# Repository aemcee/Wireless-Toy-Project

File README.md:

# Wireless-Toy-Project
ATmega328P based custom remote and unit (receiver) boards on arduino framework that will communicate over RF and with the following feature set: SD Card, RTC, Ultrasonic sensor, motor control, audio amplification w/audio jack or 8ohm speaker, motor control, LEDs

Remote PCB will replace current board in toy remote housing and receiver board will have custom 3D printed housing

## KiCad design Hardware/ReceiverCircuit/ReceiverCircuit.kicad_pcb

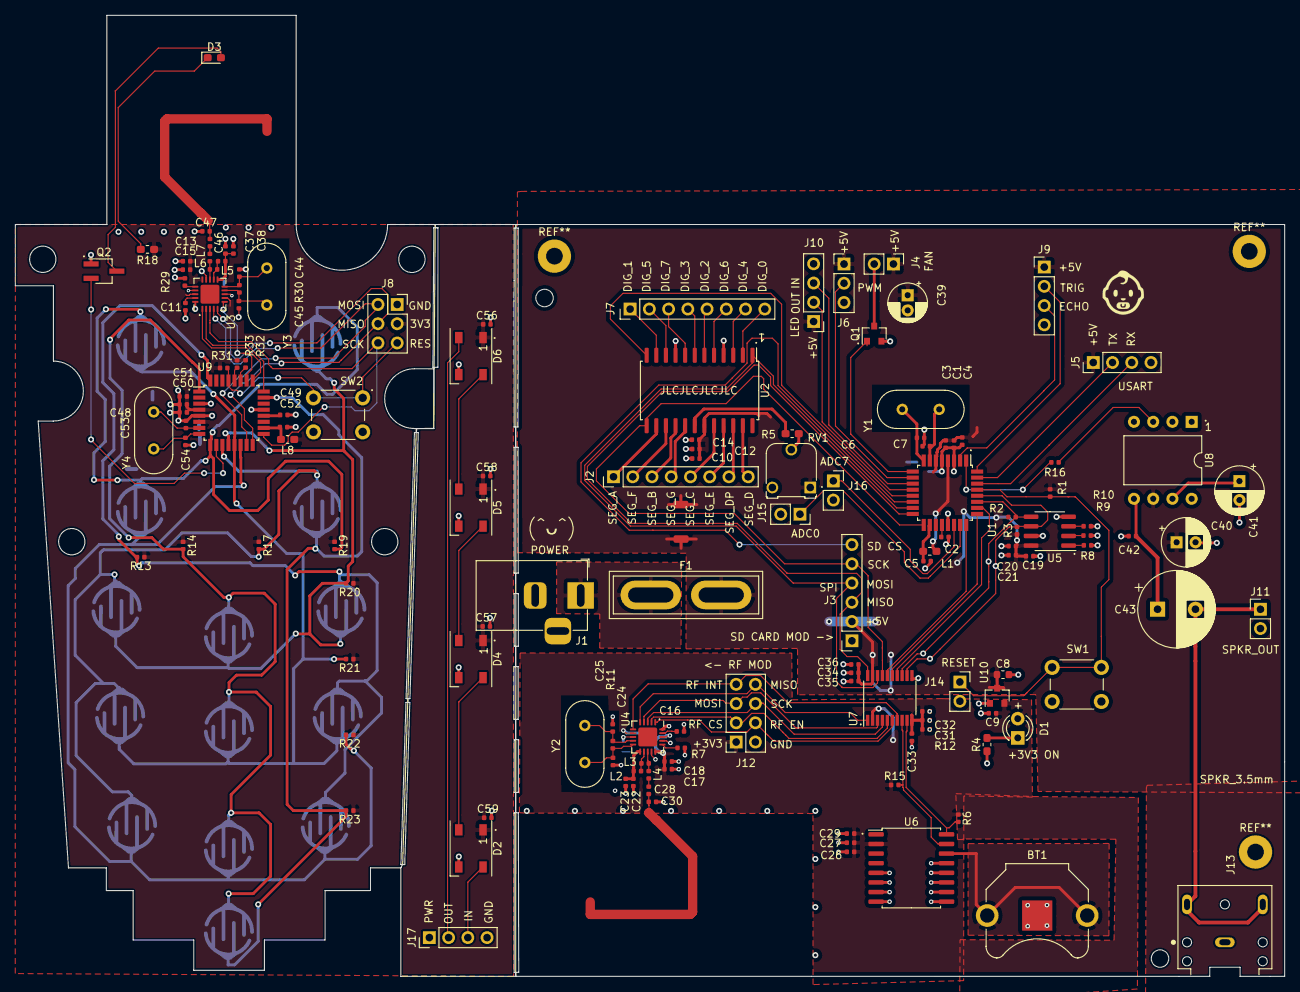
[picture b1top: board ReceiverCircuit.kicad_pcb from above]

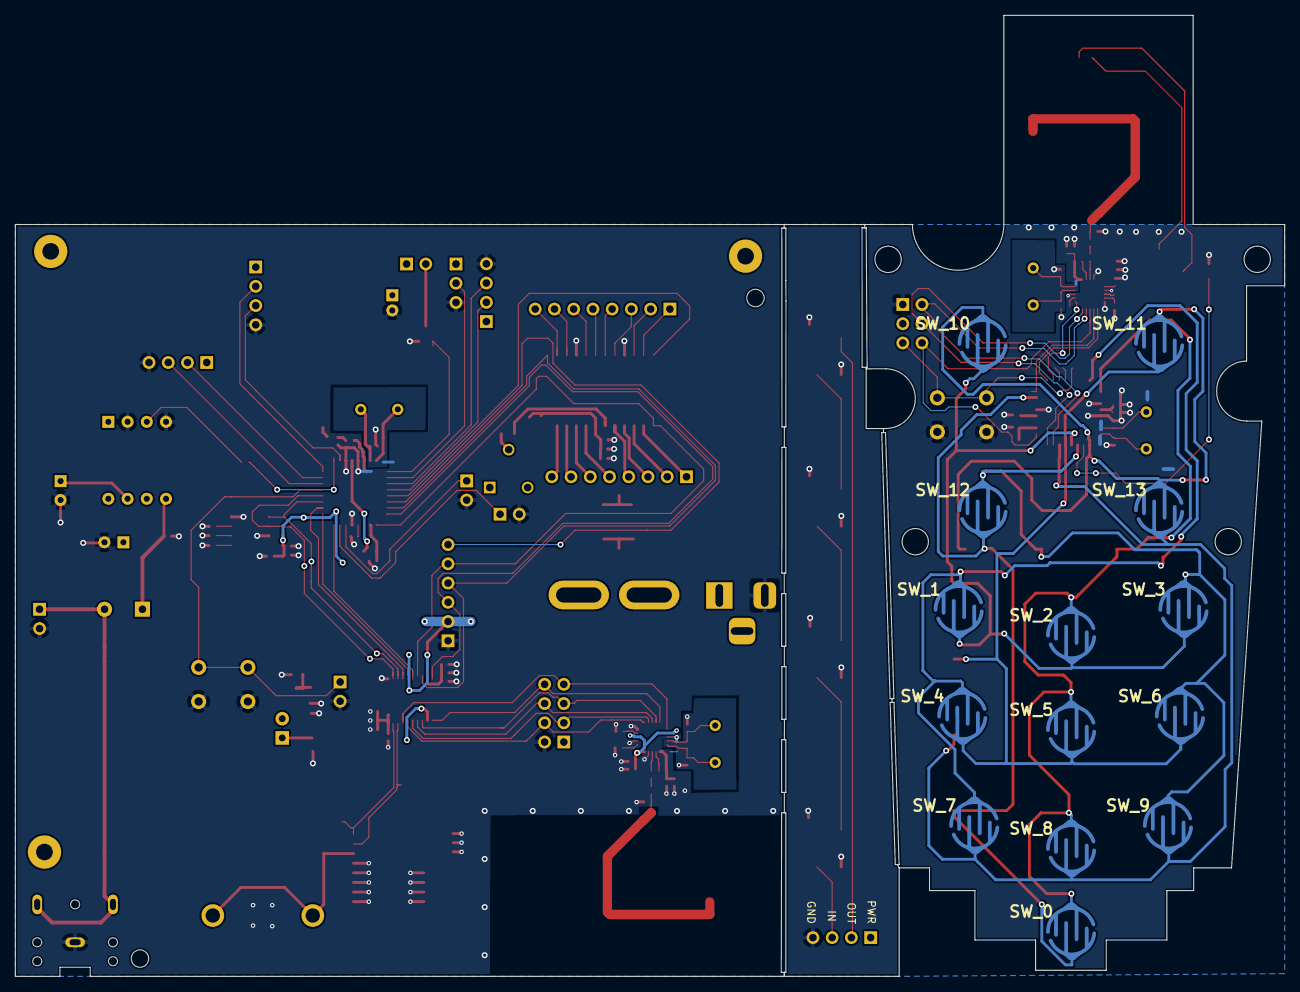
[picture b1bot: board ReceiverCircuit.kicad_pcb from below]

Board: 2 copper layers, 167.6 x 126.9 mm, 152 parts (14 on the bottom side), 114 nets.

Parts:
BT1: Battery_Cell; BatteryHolder_Keystone_3001_1x12mm
C1, C2, C10, C19, C26, C31, C34, C42, C48, C49: .1u; C_0402_1005Metric
C3, C12, C20, C27, C32, C35, C50, C56, C57, C58, C59: .01u; C_0402_1005Metric
C4, C9, C14, C21, C29, C33, C36, C51: 1u; C_0402_1005Metric
C5, C52: 0.1u; C_0402_1005Metric
C6, C7, C24, C25, C44, C45, C53, C54: 22p; C_0402_1005Metric
C8: 10u; C_0603_1608Metric
C11, C16: 33n; C_0402_1005Metric
C13, C17: 10n; C_0402_1005Metric
C15, C18: 1n; C_0402_1005Metric
C22, C37: 2.2p; C_0402_1005Metric
C23, C38: 4.7p; C_0402_1005Metric
C28, C46: 1.5p; C_0402_1005Metric
C30, C47: 1pF; C_0402_1005Metric
C39: CP_Small; CP_Radial_D5.0mm_P2.00mm
C40, C41: 100u; CP_Radial_D6.3mm_P2.50mm
C43: 1000u; CP_Radial_D10.0mm_P5.00mm
D1: LED_Small; LED_D3.0mm
D2, D4, D5, D6: WS2812B; LED_WS2812B_PLCC4_5.0x5.0mm_P3.2mm
D3: LED; LED_0603_1608Metric_Pad1.05x0.95mm_HandSolder
F1: 2A; Fuse_Blade_ATO_directSolder
J1: Jack-DC; BarrelJack_Horizontal
J2, J7: Conn_01x08; PinHeader_1x08_P2.54mm_Vertical
J3: Conn_01x06_Female; PinSocket_1x06_P2.54mm_Vertical
J4, J11: Conn_01x02; PinHeader_1x02_P2.54mm_Vertical
J5, J9: Conn_01x04; PinHeader_1x04_P2.54mm_Vertical
J6: Conn_01x03; PinHeader_1x03_P2.54mm_Vertical
J8: Conn_02x03_Odd_Even; PinSocket_2x03_P2.54mm_Vertical
J10, J17: Conn_01x04_Male; PinHeader_1x04_P2.54mm_Vertical
J12: Conn_02x04; PinSocket_2x04_P2.54mm_Vertical
J13: SJ1-3523N; CUI_SJ1-3523N
J14, J15, J16: Conn_01x02_Female; PinSocket_1x02_P2.54mm_Vertical
L1, L8: 10u; L_0603_1608Metric_Pad1.05x0.95mm_HandSolder
L2, L5: 2.7n; L_0402_1005Metric
L3, L6: 8.2n; L_0402_1005Metric
L4, L7: 3.9n; L_0402_1005Metric
Q1: Si2301CDS; SOT-23
Q2: 2N3904; SOT-23W_Handsoldering
R1, R12, R13, R14, R17, R19, R20, R21, R22, R23, R31: 10k; R_0402_1005Metric
R2, R3, R6, R8, R9, R10, R15, R32, R33: 4.7k; R_0402_1005Metric
R4, R18: 330; R_0603_1608Metric_Pad1.05x0.95mm_HandSolder
R5: R_Small; R_0603_1608Metric_Pad1.05x0.95mm_HandSolder
R7, R29: 22k; R_0402_1005Metric
R11, R30: 1M; R_0402_1005Metric
R16: 1k; R_0402_1005Metric
RV1: R_POT_Small; Potentiometer_Runtron_RM-065_Vertical
SW1, SW2: SW_Push; SW_PUSH_6mm_H5mm
SW_0, SW_1, SW_2, SW_3, SW_4, SW_5, SW_6, SW_7, SW_8, SW_9, SW_10, SW_11, SW_12, SW_13: SW_Push2; Button_Test2
U1, U9: ATmega328P-AU; TQFP-32_7x7mm_P0.8mm
U2: MAX7219; SOP-24_7.5x15.4mm_P1.27mm
U3, U4: nRF24L01P; QFN-20-1EP_4x4mm_P0.5mm_EP2.5x2.5mm
U5: AT24C256C-SSHL-T; SOIC-8_3.9x4.9mm_P1.27mm
U6: DS3231M; SOIC-16W_7.5x10.3mm_P1.27mm
U7: TXS0108EPW; TSSOP-20_4.4x6.5mm_P0.65mm
U8: LM386; DIP-8_W10.16mm
U10: TPS7A0533; SOT-23
Y1, Y2, Y3, Y4: 16MHz; Crystal_HC49-4H_Vertical

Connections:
+3.3VP: C13.1, C15.1, C48.1, C50.1, C51.1, C56.1, C57.1, C58.1, C59.1, D2.1, D4.1, D5.1, D6.1, J8.3, L8.1, R13.1, R14.1, R17.1, R18.1, R19.1, R20.1, R21.1, R22.1, R23.1, R31.1, R32.1, R33.1, U3.7, U3.15, U3.18, U9.4, U9.6
+3V3: C9.1, C17.1, C18.1, C26.1, C27.1, C29.1, C31.1, C32.1, C33.1, D1.2, J12.1, R6.1, R12.1, R15.1, U4.7, U4.15, U4.18, U6.2, U7.2, U7.10, U10.2
/Microcontroller/AREF: C2.1, U1.20
/Power/5V_IN: F1.1, J1.1
/Support ICs/RF_OUR_ANT2: C28.1, C30.2
/Trasmitter2/RF_OUR_ANT2_2: C46.1, C47.2
ADC0: J15.1, U1.23
ADC7: J16.1, U1.22
ANT1: L2.2, L3.1, U4.12
ANT1_2: L5.2, L6.1, U3.12
ANT2: L3.2, L4.2, U4.13
ANT2_2: L6.2, L7.2, U3.13
AUDIO_OUT: R16.2, U1.1
AVCC: C5.1, L1.2, U1.18
AVCC_2: C52.1, L8.2, U9.18
CL1: R13.2, SW_1.1, SW_4.1, SW_7.1, U9.32
CL2: R14.2, SW_0.1, SW_2.1, SW_5.1, SW_8.1, U9.1
CL3: R17.2, SW_3.1, SW_6.1, SW_9.1, SW_12.1, U9.11
CL4: R19.2, SW_10.1, SW_11.1, SW_13.1, U9.9
DIG_0: J7.8, U2.2
DIG_1: J7.1, U2.11
DIG_2: J7.5, U2.6
DIG_3: J7.4, U2.7
DIG_4: J7.7, U2.3
DIG_5: J7.2, U2.10
DIG_6: J7.6, U2.5
DIG_7: J7.3, U2.8
ECHO: J9.3, U1.2
FAN_CTRL: Q1.1, U1.9
FAN_GND: J4.2, Q1.3
FAN_PWR: C1.1, C3.1, C4.1, C8.1, C10.1, C12.1, C14.1, C19.1, C20.1, C21.1, C34.1, C35.1, C36.1, C39.1, C40.1, F1.2, J3.2, J4.1, J5.1, J6.1, J9.1, J10.1, J17.1, L1.1, R1.1, R2.1, R3.1, RV1.1, U1.4, U1.6, U2.19, U5.8, U7.19, U8.6, U10.3
GND: BT1.2, C1.2, C2.2, C3.2, C4.2, C5.2, C6.1, C7.1, C8.2, C9.2, C10.2, C11.2, C12.2, C13.2, C14.2, C15.2, C16.2, C17.2, C18.2, C19.2, C20.2, C21.2, C22.1, C23.1, C24.1, C25.2, C26.2, C27.2, C29.2, C30.1, C31.2, C32.2, C33.2, C34.2, C35.2, C36.2, C37.1, C38.1, C39.2, C40.2, C41.2, C42.2, C44.1, C45.2, C47.1, C48.2, C49.2, C50.2, C51.2, C52.2, C53.1, C54.1, C56.2, C57.2, C58.2, C59.2, D2.3, D4.3, D5.3, D6.3, J1.2, J3.1, J5.4, J6.3, J8.1, J9.4, J10.4, J11.2, J12.2, J13.1, J14.2, J15.2, J16.2, J17.4, Q1.2, Q2.1, R4.2, R7.2, R8.2, R9.2, R10.2, R12.2, R29.2, SW1.2, SW2.2, U1.3, U1.5, U1.21, U2.4, U2.9, U3.8, U3.14, U3.17, U3.20, U4.8, U4.14, U4.17, U4.20, U5.4, U5.7, U6.5, U6.6, U6.7, U6.8, U6.9, U6.10, U6.11, U6.12, U6.13, U7.11, U8.2, U8.4, U9.3, U9.5, U9.21, U10.1
LED_DATA2_IN: D2.4, J17.3
LED_DATA2_OUT: D6.2, J17.2
LED_DATA_IN: J10.3, U1.11
LED_DATA_OUT: J10.2, U1.12
LED_LOAD: U1.13, U2.12
MISO_3V3: J12.8, U4.5, U7.1
MISO_3V3_2: J8.4, U3.5, U9.16
MISO_5V: J3.3, U1.16, U7.20
MOSI_3V3: J12.5, U4.4, U7.3
MOSI_3V3_2: J8.2, U3.4, U9.15
MOSI_5V: J3.4, U1.15, U2.1, U7.18
unnamed: BT1.1, U6.14
unnamed: C11.1, U3.19
unnamed: C16.1, U4.19
unnamed: C24.2, R11.1, U4.10, Y2.2
unnamed: C25.1, R11.2, U4.9, Y2.1
unnamed: C28.2, L4.1
unnamed: C41.1, U8.7
unnamed: C42.1, C43.1, U8.5
unnamed: C44.2, R30.1, U3.10, Y3.2
unnamed: C45.1, R30.2, U3.9, Y3.1
unnamed: C46.2, L7.1
unnamed: C49.1, U9.20
unnamed: D1.1, R4.1
unnamed: D2.2, D4.4
unnamed: D3.1, R18.2
unnamed: D3.2, Q2.3
unnamed: D4.2, D5.4
unnamed: D5.2, D6.4
unnamed: Q2.2, U9.10
unnamed: R5.1, RV1.2
unnamed: R5.2, U2.18
unnamed: R7.1, U4.16
unnamed: R8.1, U5.1
unnamed: R9.1, U5.2
unnamed: R10.1, U5.3
unnamed: R16.1, U8.3
unnamed: R29.1, U3.16
PEN_PWM: J6.2, U1.10
RA1: R20.2, SW_1.2, SW_2.2, SW_3.2, SW_10.2, U9.12
RA2: R21.2, SW_4.2, SW_5.2, SW_6.2, SW_11.2, U9.13
RA3: R22.2, SW_7.2, SW_8.2, SW_9.2, SW_13.2, U9.14
RA4: R23.2, SW_0.2, SW_12.2, U9.23
RESET: J14.1, R1.2, SW1.1, U1.29
RESET_2: J8.5, R31.2, SW2.1, U9.29
RF_EN_3V3: J12.4, U4.1, U7.6
RF_EN_3V3_2: U3.1, U9.25
RF_EN_5V: U1.25, U7.15
RF_INT_3V3: J12.7, U4.6, U7.7
RF_INT_3V3_2: U3.6, U9.26
RF_INT_5V: U1.26, U7.14
SCK_3V3: J12.6, U4.3, U7.4
SCK_3V3_2: J8.6, U3.3, U9.17
SCK_5V: J3.5, U1.17, U2.13, U7.17
SCL_2: R33.2, U9.28
SCL_3V3: R6.2, U6.16, U7.9
SCL_5V: R3.2, U1.28, U5.6, U7.12
SDA_2: R32.2, U9.27
SDA_3V3: R15.2, U6.15, U7.8
SDA_5V: R2.2, U1.27, U5.5, U7.13
SEG_A: J2.1, U2.14
SEG_B: J2.3, U2.16
SEG_C: J2.5, U2.20
SEG_D: J2.8, U2.23
SEG_DP: J2.7, U2.22
SEG_E: J2.6, U2.21
SEG_F: J2.2, U2.15
SEG_G: J2.4, U2.17
SPKR_OUT: C43.2, J11.1, J13.2, J13.3
SS_RF_3V3: J12.3, U4.2, U7.5
SS_RF_3V3_2: U3.2, U9.24
SS_RF_5V: U1.24, U7.16
SS_SD_CARD_5V: J3.6, U1.14
TRIG: J9.2, U1.32
USART_RX: J5.3, U1.30
USART_TX: J5.2, U1.31
VDD_PA: C22.2, C23.2, L2.1, U4.11
VDD_PA_2: C37.2, C38.2, L5.1, U3.11
uP_OSC1: C6.2, U1.7, Y1.1
uP_OSC1_2: C53.2, U9.7, Y4.1
uP_OSC2: C7.2, U1.8, Y1.2
uP_OSC2_2: C54.2, U9.8, Y4.2

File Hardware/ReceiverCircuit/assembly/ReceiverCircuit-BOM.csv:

Comment,Designator,Footprint,LCSC
"Battery_Cell","BT1","Battery:BatteryHolder_Keystone_3001_1x12mm",""
".1u","C1,C2,C10,C19,C26,C31,C34,C42","Capacitor_SMD:C_0402_1005Metric","C1525"
"33n","C16","Capacitor_SMD:C_0402_1005Metric","C1585"
"10n","C17","Capacitor_SMD:C_0402_1005Metric","C15195"
"1n","C18","Capacitor_SMD:C_0402_1005Metric","C1523"
"2.2p","C22","Capacitor_SMD:C_0402_1005Metric","C1559"
"4.7p","C23","Capacitor_SMD:C_0402_1005Metric","C1569"
"1.5p","C28","Capacitor_SMD:C_0402_1005Metric","C1552"
".01u","C3,C12,C20,C27,C32,C35","Capacitor_SMD:C_0402_1005Metric","C15195"
"1pF","C30","Capacitor_SMD:C_0402_1005Metric","C1550"
"CP_Small","C39","Capacitor_THT:CP_Radial_D5.0mm_P2.00mm",""
"1u","C4,C9,C14,C21,C29,C33,C36","Capacitor_SMD:C_0402_1005Metric","C52923"
"100u","C40,C41","Capacitor_THT:CP_Radial_D6.3mm_P2.50mm",""
"1000u","C43","Capacitor_THT:CP_Radial_D10.0mm_P5.00mm",""
"0.1u","C5","Capacitor_SMD:C_0402_1005Metric","C1525"
"22p","C6,C7,C24,C25","Capacitor_SMD:C_0402_1005Metric","C1555"
"10u","C8","Capacitor_SMD:C_0603_1608Metric","C19702"
"LED_Small","D1","LED_THT:LED_D3.0mm",""
"2A","F1","Fuse:Fuse_Blade_ATO_directSolder",""
"Jack-DC","J1","Connector_BarrelJack:BarrelJack_Horizontal",""
"Conn_01x04_Male","J10","Connector_PinHeader_2.54mm:PinHeader_1x04_P2.54mm_Vertical",""
"Conn_02x04","J12","Connector_PinSocket_2.54mm:PinSocket_2x04_P2.54mm_Vertical",""
"SJ1-3523N","J13","ProjectFootprint:CUI_SJ1-3523N",""
"Conn_01x02_Female","J14,J15,J16","Connector_PinSocket_2.54mm:PinSocket_1x02_P2.54mm_Vertical",""
"Conn_01x06_Female","J3","Connector_PinSocket_2.54mm:PinSocket_1x06_P2.54mm_Vertical",""
"Conn_01x02","J4,J11","Connector_PinHeader_2.54mm:PinHeader_1x02_P2.54mm_Vertical",""
"Conn_01x04","J5,J9","Connector_PinHeader_2.54mm:PinHeader_1x04_P2.54mm_Vertical",""
"Conn_01x03","J6","Connector_PinHeader_2.54mm:PinHeader_1x03_P2.54mm_Vertical",""
"Conn_01x08","J2,J7","Connector_PinHeader_2.54mm:PinHeader_1x08_P2.54mm_Vertical",""
"10u","L1","Inductor_SMD:L_0603_1608Metric_Pad1.05x0.95mm_HandSolder",""
"2.7n","L2","Inductor_SMD:L_0402_1005Metric","C27123"
"8.2n","L3","Inductor_SMD:L_0402_1005Metric","C16208"
"3.9n","L4","Inductor_SMD:L_0402_1005Metric","C14033"
"Si2301CDS","Q1","Package_TO_SOT_SMD:SOT-23","C10487"
"10k","R1,R12","Resistor_SMD:R_0402_1005Metric","C25744"
"1M","R11","Resistor_SMD:R_0402_1005Metric","C26083"
"1k","R16","Resistor_SMD:R_0402_1005Metric","C11702"
"4.7k","R2,R3,R6,R8,R9,R10,R15","Resistor_SMD:R_0402_1005Metric","C25900"
"330","R4","Resistor_SMD:R_0603_1608Metric_Pad1.05x0.95mm_HandSolder",""
"R_Small","R5","Resistor_SMD:R_0603_1608Metric_Pad1.05x0.95mm_HandSolder",""
"22k","R7","Resistor_SMD:R_0402_1005Metric","C25768"
"R_POT_Small","RV1","Potentiometer_THT:Potentiometer_Runtron_RM-065_Vertical",""
"SW_Push","SW1","Button_Switch_THT:SW_PUSH_6mm_H5mm",""
"ATmega328P-AU","U1","Package_QFP:TQFP-32_7x7mm_P0.8mm","C14877"
"TPS7A0533","U10","Package_TO_SOT_SMD:SOT-23",""
"MAX7219","U2","Package_SO:SOP-24_7.5x15.4mm_P1.27mm",""
"nRF24L01P","U4","Package_DFN_QFN:QFN-20-1EP_4x4mm_P0.5mm_EP2.5x2.5mm","C8791"
"AT24C256C-SSHL-T","U5","Package_SO:SOIC-8_3.9x4.9mm_P1.27mm","C6482"
"DS3231M","U6","Package_SO:SOIC-16W_7.5x10.3mm_P1.27mm","C37663"
"TXS0108EPW","U7","Package_SO:TSSOP-20_4.4x6.5mm_P0.65mm","C17206"
"LM386","U8","Package_DIP:DIP-8_W10.16mm",""
"16MHz","Y1,Y2","Crystal:Crystal_HC49-4H_Vertical",""

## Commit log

2021-02-18 Added tone melody test code
    Test code is modified for use on the unit board
2021-02-18 RF_Sample_Code_For_RX_TX
2021-02-19 added test text
2021-02-20 Add Wireless Toy Project Structure
2021-02-20 Added Hardware Software Directories
2021-02-20 Create Software
2021-02-21 Renamed Directory Sofware to Software
2021-03-05 Add files via upload
    Initial code to test button array functionality.
2021-03-13 Added comments
2021-03-13 added test.txt
2021-04-20 added music player
2021-04-20 added tone test
2021-06-05 Add files via upload
    TX has code to support LED control at RX
2021-06-13 Added RX and TX code modified with Music Player
2021-06-13 adding RF TX and RX
2021-06-13 Added PCB Files
2021-06-13 Update Readme with project description
2021-11-23 Added PCB img
2021-11-24 Updated README w/vid
